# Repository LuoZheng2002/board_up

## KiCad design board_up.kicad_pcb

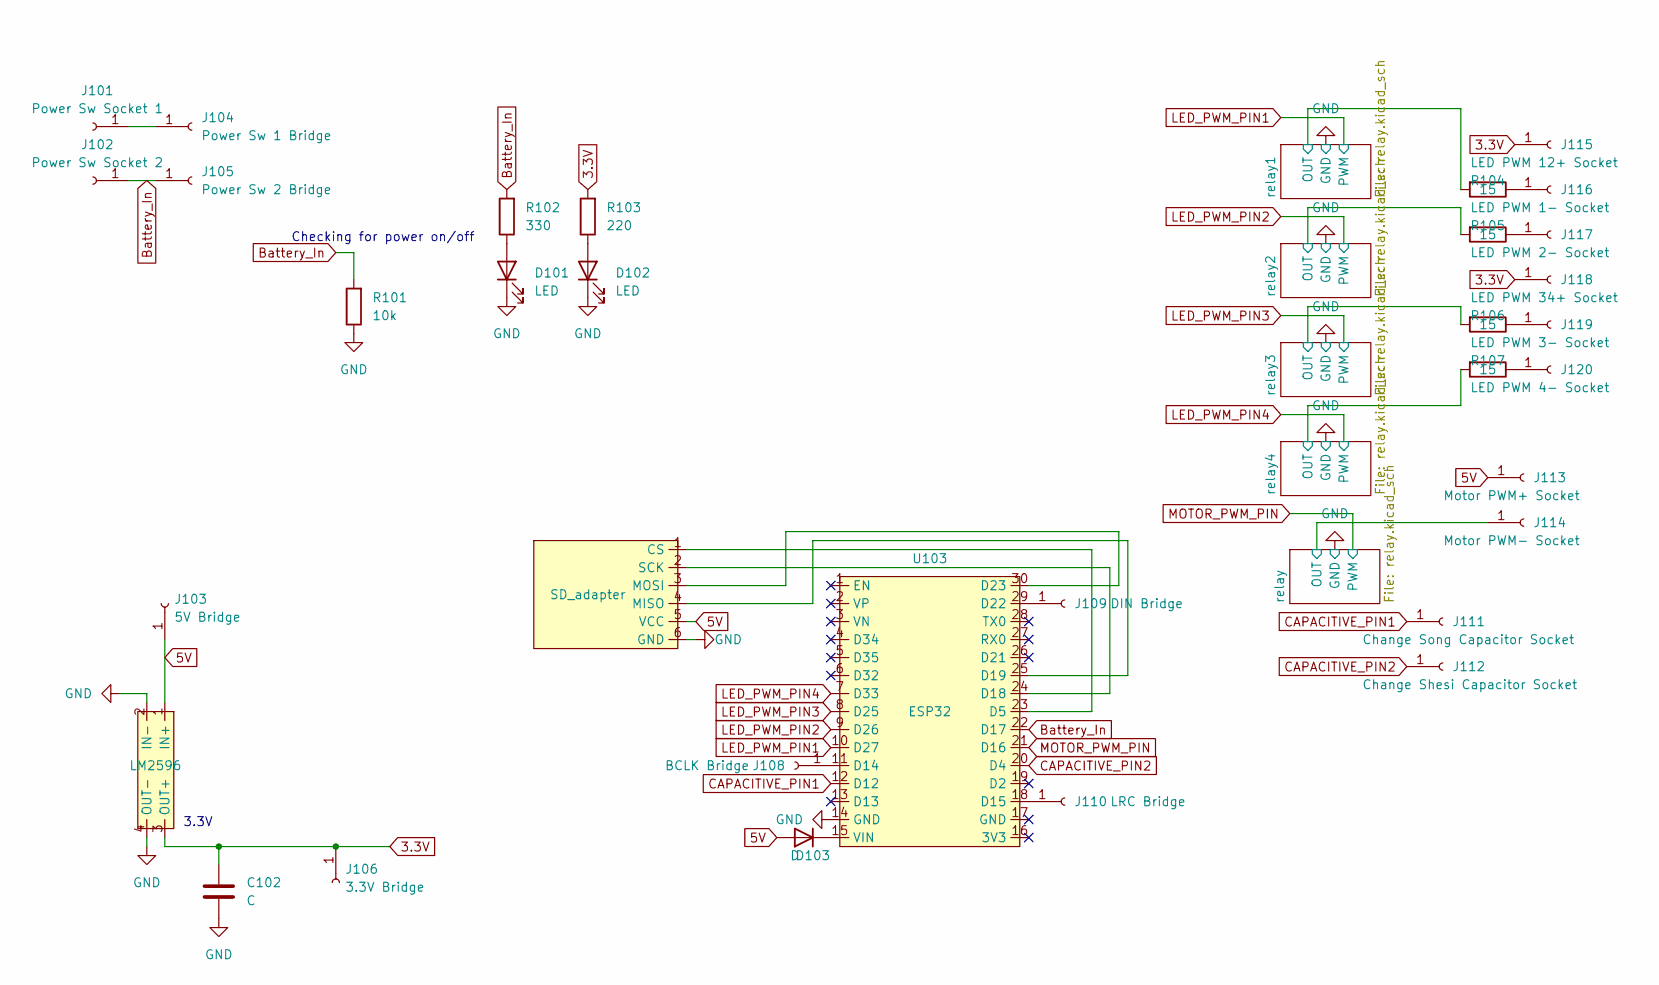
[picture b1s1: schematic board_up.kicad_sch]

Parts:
C102: C; CP_Radial_D5.0mm_P2.50mm
D101, D102: LED; LED_D5.0mm
D103: D; D_DO-34_SOD68_P7.62mm_Horizontal
J101: Power Sw Socket 1; PinSocket_1x01_P2.54mm_Vertical
J102: Power Sw Socket 2; PinSocket_1x01_P2.54mm_Vertical
J103: 5V Bridge; PinSocket_1x01_P2.54mm_Vertical
J104: Power Sw 1 Bridge; PinSocket_1x01_P2.54mm_Vertical
J105: Power Sw 2 Bridge; PinSocket_1x01_P2.54mm_Vertical
J106: 3.3V Bridge; PinSocket_1x01_P2.54mm_Vertical
J108: BCLK Bridge; PinSocket_1x01_P2.54mm_Vertical
J109: DIN Bridge; PinSocket_1x01_P2.54mm_Vertical
J110: LRC Bridge; PinSocket_1x01_P2.54mm_Vertical
J111: Change Song Capacitor Socket; PinSocket_1x01_P2.54mm_Vertical
J112: Change Shesi Capacitor Socket; PinSocket_1x01_P2.54mm_Vertical
J113: Motor PWM+ Socket; PinSocket_1x01_P2.54mm_Vertical
J114: Motor PWM- Socket; PinSocket_1x01_P2.54mm_Vertical
J115: LED PWM 12+ Socket; PinSocket_1x01_P2.54mm_Vertical
J116: LED PWM 1- Socket; PinSocket_1x01_P2.54mm_Vertical
J117: LED PWM 2- Socket; PinSocket_1x01_P2.54mm_Vertical
J118: LED PWM 34+ Socket; PinSocket_1x01_P2.54mm_Vertical
J119: LED PWM 3- Socket; PinSocket_1x01_P2.54mm_Vertical
J120: LED PWM 4- Socket; PinSocket_1x01_P2.54mm_Vertical
R101: 10k; R_Axial_DIN0207_L6.3mm_D2.5mm_P7.62mm_Horizontal
R102: 330; R_Axial_DIN0207_L6.3mm_D2.5mm_P7.62mm_Horizontal
R103: 220; R_Axial_DIN0207_L6.3mm_D2.5mm_P7.62mm_Horizontal
R104, R105, R106, R107: 15; R_Axial_DIN0207_L6.3mm_D2.5mm_P7.62mm_Horizontal
U101: LM2596
U102: SD_adapter; SD_Adapter
U103: ESP32; ESP32_30PIN

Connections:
3.3V: C102.1, J106.1, J115.1, J118.1, R103.2, U101.3 (OUT+)
5V: D103.2 (A), J103.1, J113.1, U101.1 (IN+), U102.5 (VCC)
/relay1/OUT: R104.2; also elsewhere on the board
/relay2/OUT: R105.2; also elsewhere on the board
/relay3/OUT: R106.2; also elsewhere on the board
/relay4/OUT: R107.2; also elsewhere on the board
/relay/OUT: J114.1; also elsewhere on the board
Battery_In: J102.1, J105.1, R101.2, R102.2, U103.22 (D17)
CAPACITIVE_PIN1: J111.1, U103.12 (D12)
CAPACITIVE_PIN2: J112.1, U103.20 (D4)
GND: C102.2, D101.1 (K), D102.1 (K), R101.1, U101.2 (IN-), U101.4 (OUT-), U102.6 (GND), U103.14 (GND); also elsewhere on the board
LED_PWM_PIN1: U103.10 (D27); also elsewhere on the board
LED_PWM_PIN2: U103.9 (D26); also elsewhere on the board
LED_PWM_PIN3: U103.8 (D25); also elsewhere on the board
LED_PWM_PIN4: U103.7 (D33); also elsewhere on the board
MOTOR_PWM_PIN: U103.21 (D16); also elsewhere on the board
unnamed: D101.2 (A), R102.1
unnamed: D102.2 (A), R103.1
unnamed: D103.1 (K), U103.15 (VIN)
unnamed: J101.1, J104.1
unnamed: J108.1, U103.11 (D14)
unnamed: J109.1, U103.29 (D22)
unnamed: J110.1, U103.18 (D15)
unnamed: J116.1, R104.1
unnamed: J117.1, R105.1
unnamed: J119.1, R106.1
unnamed: J120.1, R107.1
unnamed: U102.1 (CS), U103.23 (D5)
unnamed: U102.4 (MISO), U103.25 (D19)
unnamed: U102.3 (MOSI), U103.30 (D23)
unnamed: U102.2 (SCK), U103.24 (D18)

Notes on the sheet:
Checking for power on/off
3.3V

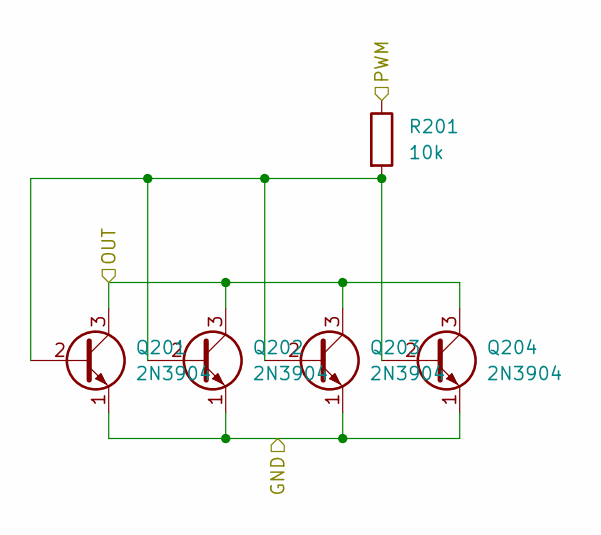
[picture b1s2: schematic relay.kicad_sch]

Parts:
Q201, Q202, Q203, Q204: 2N3904; TO-92_Inline
R201: 10k; R_Axial_DIN0207_L6.3mm_D2.5mm_P7.62mm_Horizontal

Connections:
/relay1/OUT: Q201.3 (C), Q202.3 (C), Q203.3 (C), Q204.3 (C); also elsewhere on the board
GND: Q201.1 (E), Q202.1 (E), Q203.1 (E), Q204.1 (E); also elsewhere on the board
LED_PWM_PIN1: R201.1; also elsewhere on the board
unnamed: Q201.2 (B), Q202.2 (B), Q203.2 (B), Q204.2 (B), R201.2

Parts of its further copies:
Q301, Q302, Q303, Q304, Q401, Q402, Q403, Q404, Q501, Q502, Q503, Q504, Q601, Q602, Q603, Q604: 2N3904; TO-92_Inline
R301, R401, R501, R601: 10k; R_Axial_DIN0207_L6.3mm_D2.5mm_P7.62mm_Horizontal

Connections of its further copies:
/relay2/OUT: Q401.3 (C), Q402.3 (C), Q403.3 (C), Q404.3 (C); also elsewhere on the board
/relay3/OUT: Q501.3 (C), Q502.3 (C), Q503.3 (C), Q504.3 (C); also elsewhere on the board
/relay4/OUT: Q601.3 (C), Q602.3 (C), Q603.3 (C), Q604.3 (C); also elsewhere on the board
/relay/OUT: Q301.3 (C), Q302.3 (C), Q303.3 (C), Q304.3 (C); also elsewhere on the board
GND: Q301.1 (E), Q302.1 (E), Q303.1 (E), Q304.1 (E), Q401.1 (E), Q402.1 (E), Q403.1 (E), Q404.1 (E), Q501.1 (E), Q502.1 (E), Q503.1 (E), Q504.1 (E), Q601.1 (E), Q602.1 (E), Q603.1 (E), Q604.1 (E); also elsewhere on the board
LED_PWM_PIN2: R401.1; also elsewhere on the board
LED_PWM_PIN3: R501.1; also elsewhere on the board
LED_PWM_PIN4: R601.1; also elsewhere on the board
MOTOR_PWM_PIN: R301.1; also elsewhere on the board
unnamed: Q301.2 (B), Q302.2 (B), Q303.2 (B), Q304.2 (B), R301.2
unnamed: Q401.2 (B), Q402.2 (B), Q403.2 (B), Q404.2 (B), R401.2
unnamed: Q501.2 (B), Q502.2 (B), Q503.2 (B), Q504.2 (B), R501.2
unnamed: Q601.2 (B), Q602.2 (B), Q603.2 (B), Q604.2 (B), R601.2

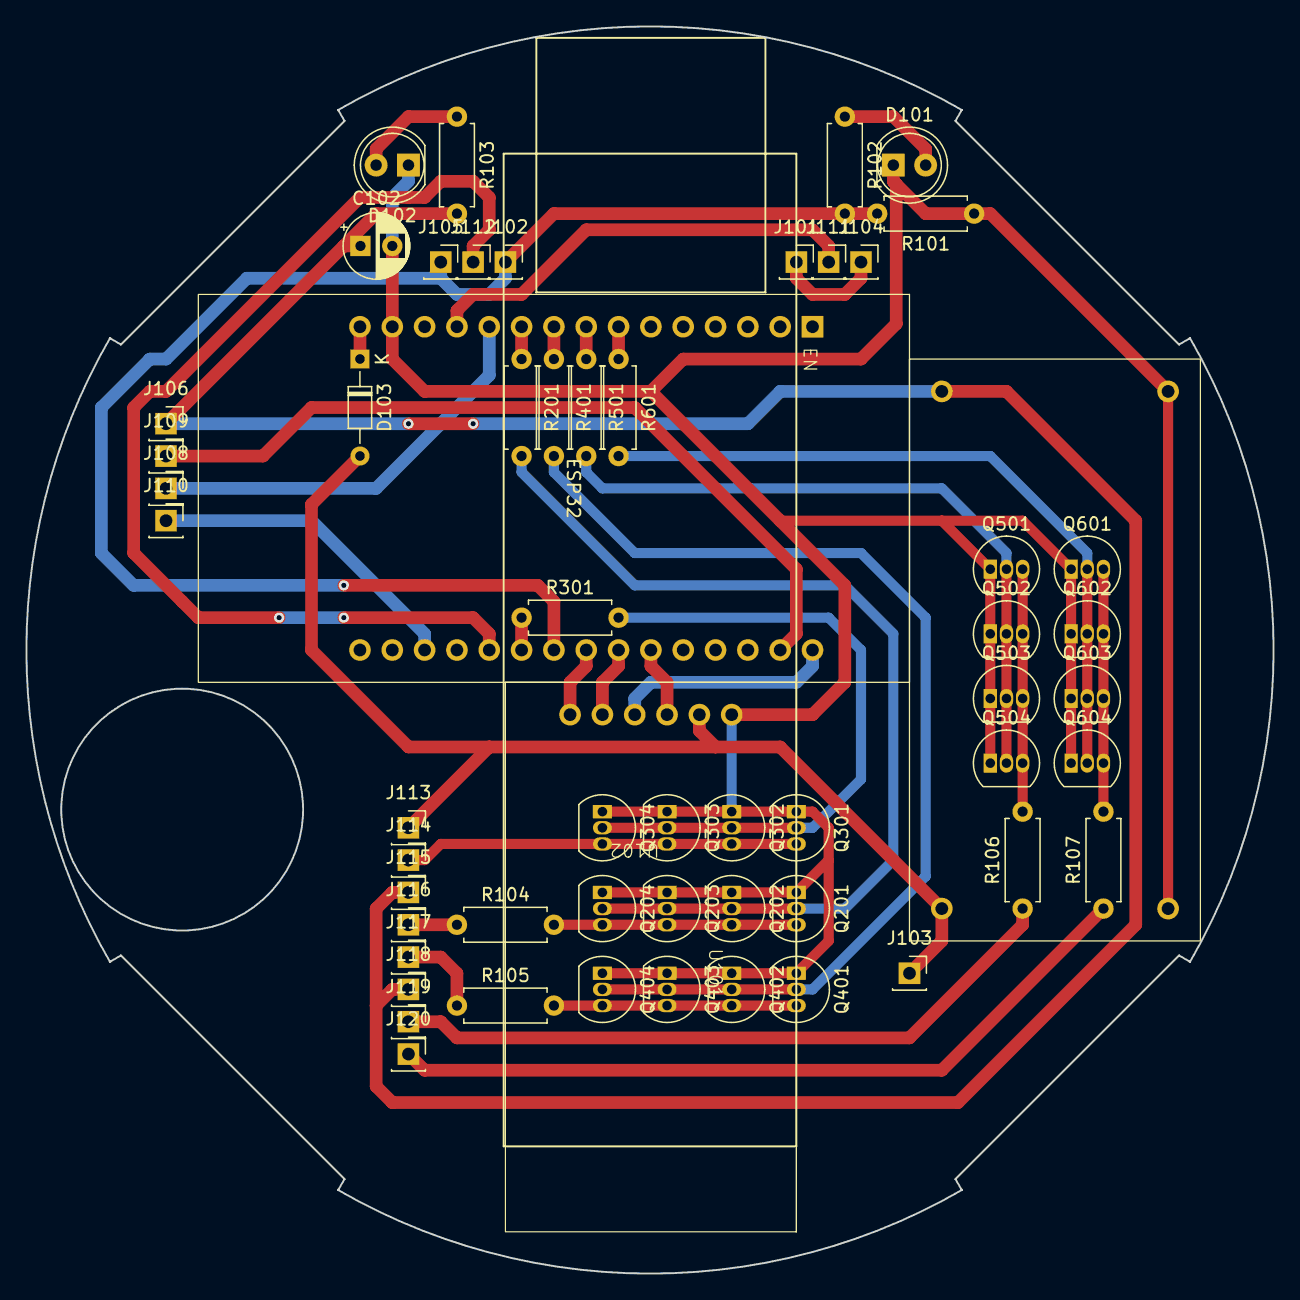
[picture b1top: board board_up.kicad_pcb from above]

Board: 2 copper layers, 98.0 x 98.0 mm, 58 parts (0 on the bottom side), 36 nets.

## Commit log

2024-02-07 checkpoint
